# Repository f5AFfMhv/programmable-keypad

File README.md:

# Programmabe Keypad
This is keypad project which uses Arduino Pro Micro as keyboard emulator. Each button sends key press combination over USB which is mapped to some particular action on computer.

Some footprints in this project are custom ones. You will need to import [my footprints](https://github.com/f5AFfMhv/my-kicad-libraries) library into KiCad.

For more information about this project look at its instructables page:
* [Programmable Keypad Rev B](https://www.instructables.com/Programmable-Keypad-Rev-B/)
* [Programmable Keypad](https://www.instructables.com/Programmable-Keypad-1/)

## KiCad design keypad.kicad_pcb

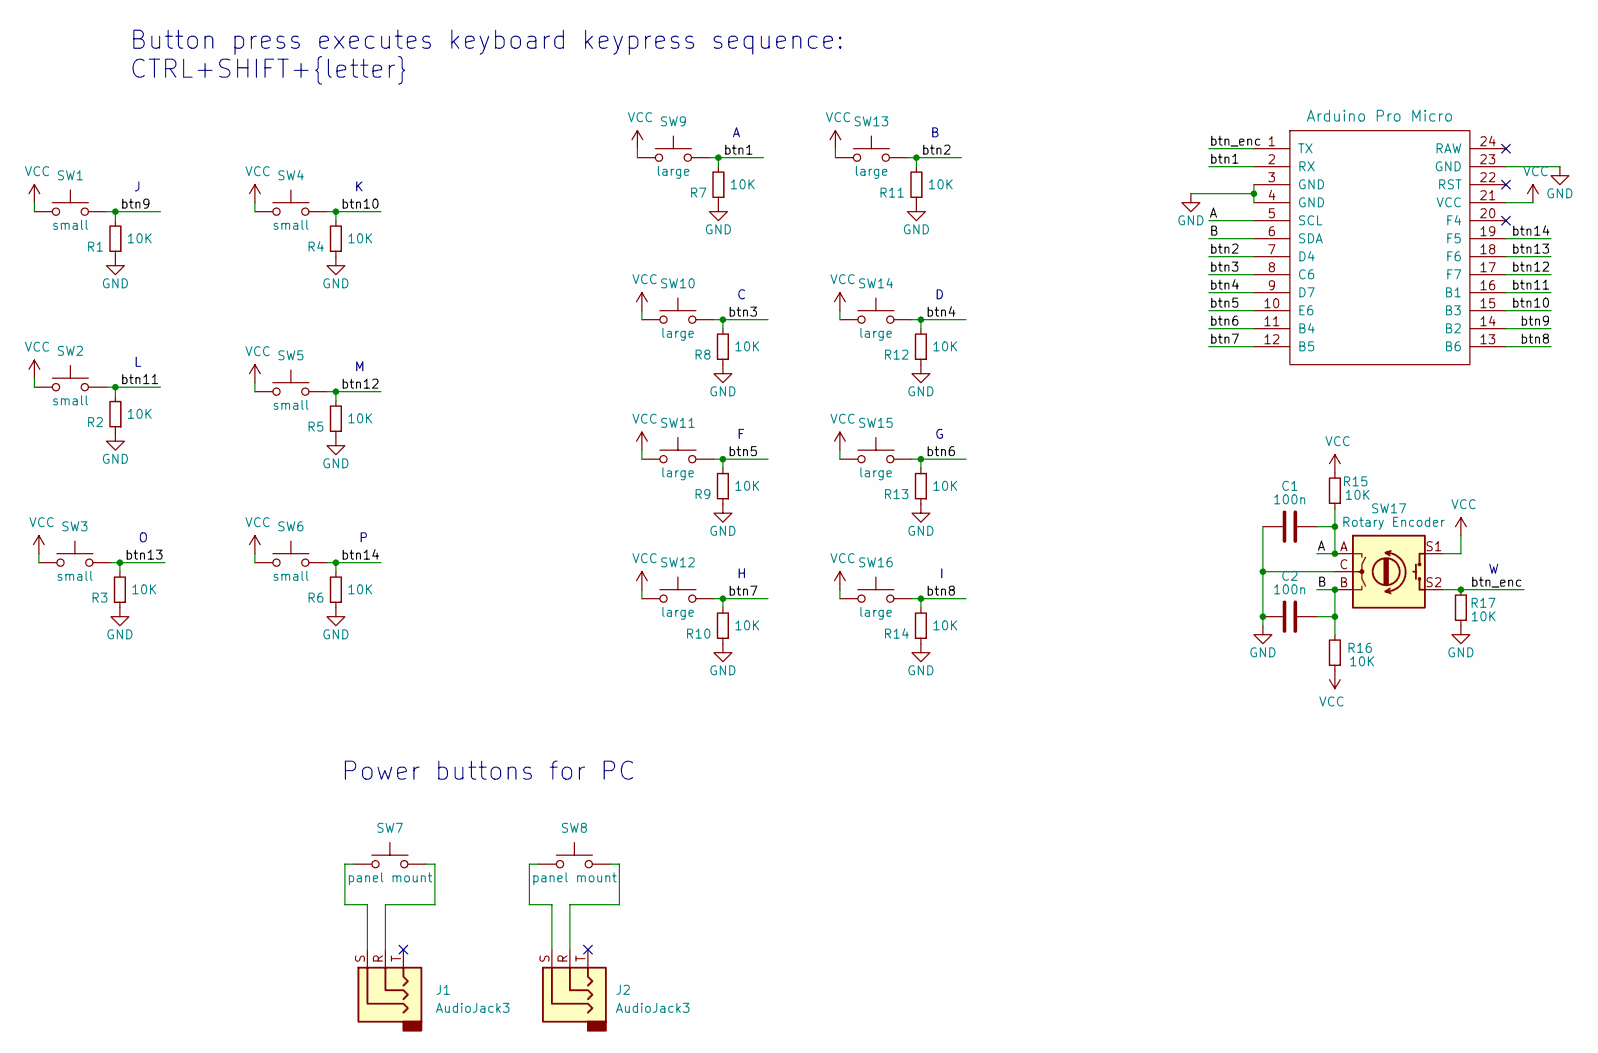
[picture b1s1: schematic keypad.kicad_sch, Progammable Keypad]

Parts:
C1, C2: 100n; C_0805_2012Metric
J1, J2: AudioJack3; Jack_3.5mm_custom-SMT_Horizontal
R1, R2, R3, R4, R5, R6, R7, R8, R9, R10, R11, R12, R13, R14, R15, R16, R17: 10K; R_0805_2012Metric
SW1, SW2, SW3, SW4, SW5, SW6: SW_Push; SW_SPST_PTS645
SW7, SW8: SW_Push; SW_SPST_button_panel-mount-12mm
SW9, SW10, SW11, SW12, SW13, SW14, SW15, SW16: SW_Push; SW_SPST_button_12x12_smd
SW17: Rotary Encoder; RotaryEncoder_custom
U1: Arduino Pro Micro; ProMicro-SMD

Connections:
/A: C1.1, R15.1, SW17.A, U1.5 (SCL)
/B: C2.1, R16.2, SW17.B, U1.6 (SDA)
/btn1: R7.2, SW9.2, U1.2 (RX)
/btn2: R11.2, SW13.2, U1.7 (D4)
/btn3: R8.2, SW10.2, U1.8 (C6)
/btn4: R12.2, SW14.2, U1.9 (D7)
/btn5: R9.2, SW11.2, U1.10 (E6)
/btn6: R13.2, SW15.2, U1.11 (B4)
/btn7: R10.2, SW12.2, U1.12 (B5)
/btn8: R14.2, SW16.2, U1.13 (B6)
/btn9: R1.2, SW1.2, U1.14 (B2)
/btn10: R4.2, SW4.2, U1.15 (B3)
/btn11: R2.2, SW2.2, U1.16 (B1)
/btn12: R5.2, SW5.2, U1.17 (F7)
/btn13: R3.2, SW3.2, U1.18 (F6)
/btn14: R6.2, SW6.2, U1.19 (F5)
/btn_enc: R17.2, SW17.S2, U1.1 (TX)
GND: C1.2, C2.2, R1.1, R2.1, R3.1, R4.1, R5.1, R6.1, R7.1, R8.1, R9.1, R10.1, R11.1, R12.1, R13.1, R14.1, R17.1, SW17.C, U1.3 (GND), U1.4 (GND), U1.23 (GND)
unnamed: J1.R, SW7.2
unnamed: J1.S, SW7.1
unnamed: J2.R, SW8.2
unnamed: J2.S, SW8.1
VCC: R15.2, R16.1, SW1.1, SW2.1, SW3.1, SW4.1, SW5.1, SW6.1, SW9.1, SW10.1, SW11.1, SW12.1, SW13.1, SW14.1, SW15.1, SW16.1, SW17.S1, U1.21 (VCC)

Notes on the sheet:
Button press executes keyboard keypress sequence: CTRL+SHIFT+{letter}
Power buttons for PC

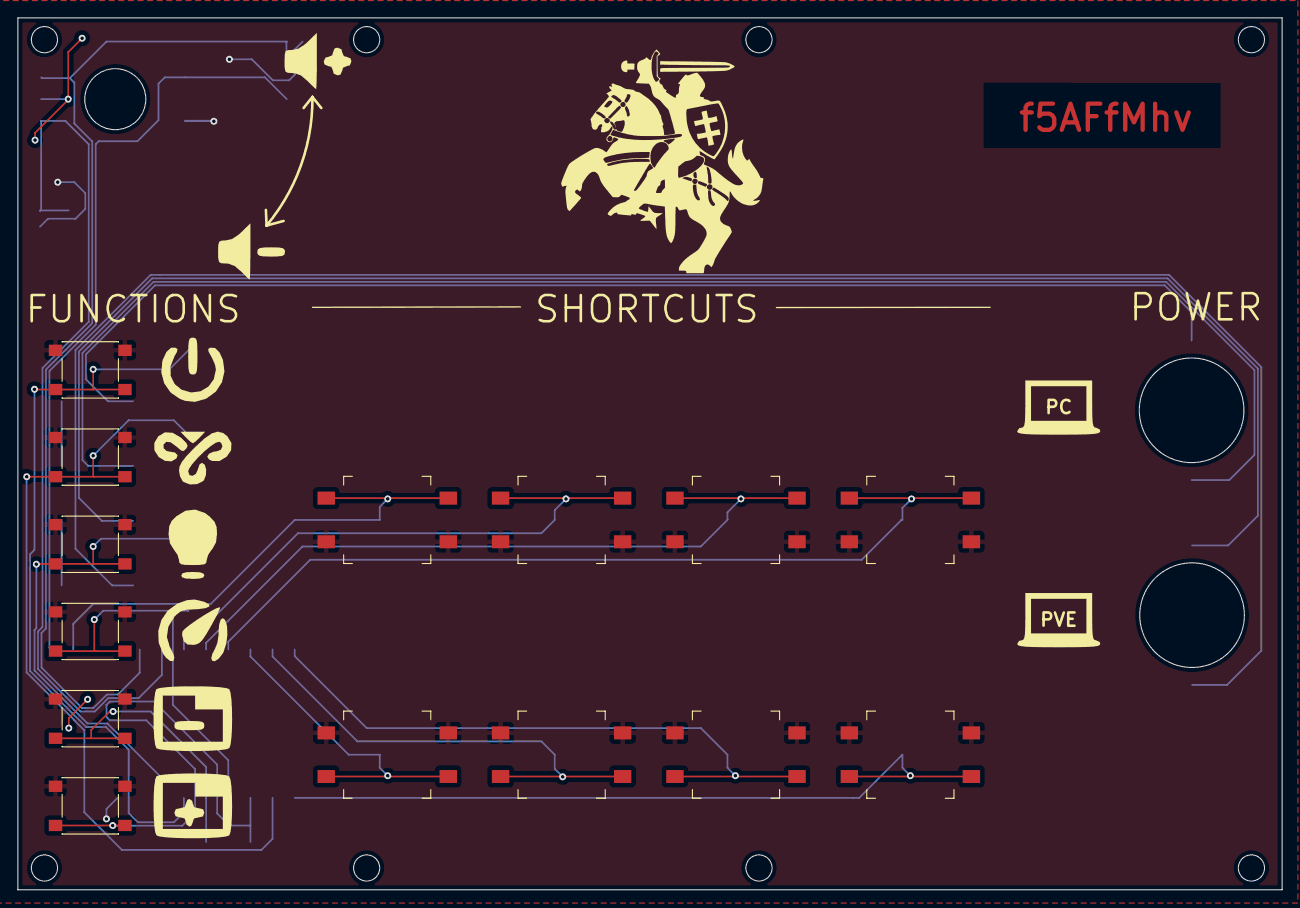
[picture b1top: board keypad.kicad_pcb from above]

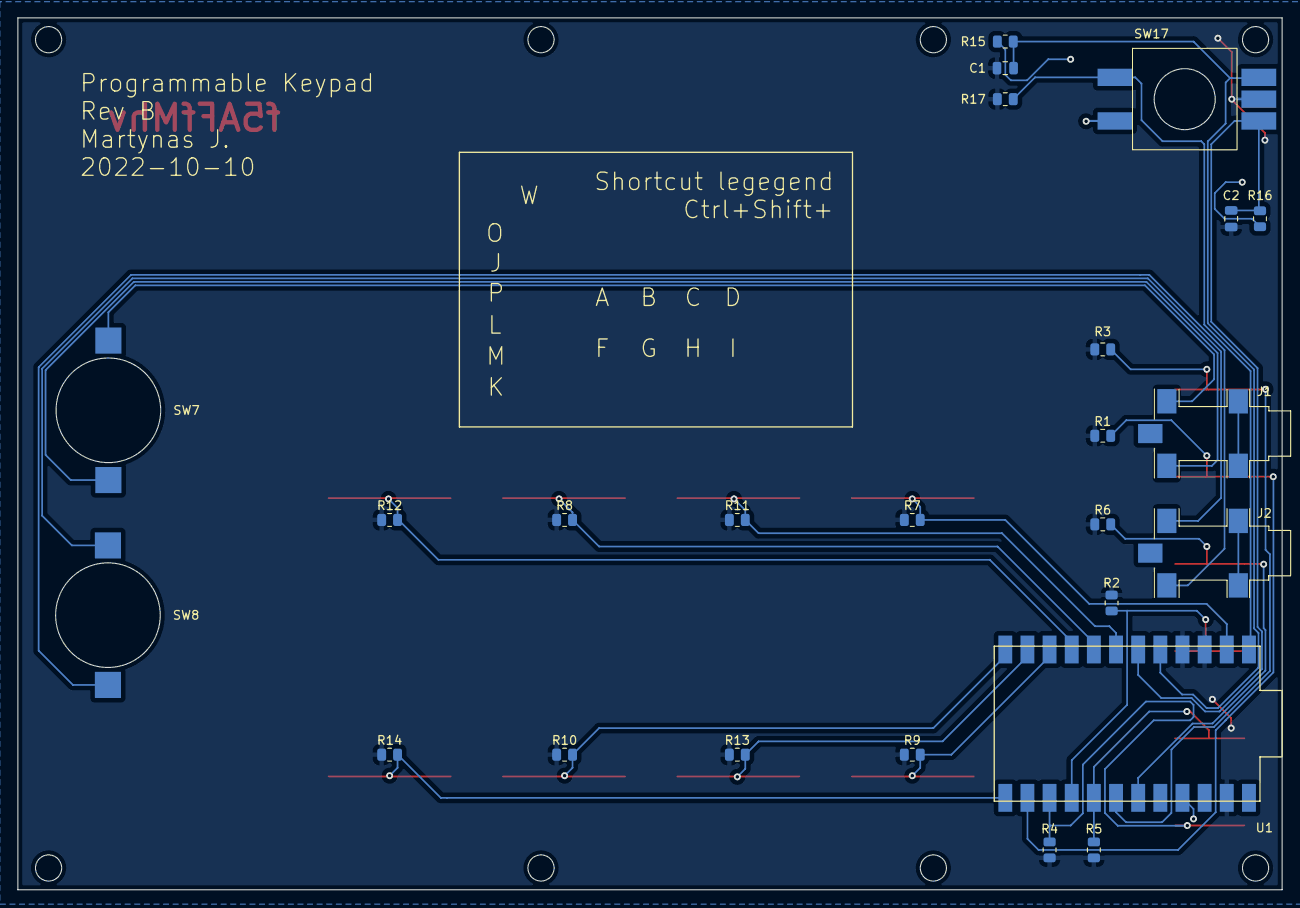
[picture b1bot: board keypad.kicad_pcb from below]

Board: 2 copper layers, 145.0 x 100.0 mm, 41 parts (22 on the bottom side), 23 nets.

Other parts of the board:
PC: LOGO; pc-symbol
PVE: LOGO; pc-symbol

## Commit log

2022-11-27 add link too footprints
2022-11-28 add link to Rev B instructables
2022-11-28 change second encoder function
